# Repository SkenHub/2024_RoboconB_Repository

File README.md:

# 2024_RoboconB_Repository
2024年ロボコンBチーム共有用リポジトリ

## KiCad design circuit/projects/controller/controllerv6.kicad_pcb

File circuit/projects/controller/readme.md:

# 回路系のピン
## コントローラ  
buttonPin1 = 35; 
buttonPin2 = 26;
buttonPin3 = 33;
buttonPin4 = 25;
buttonPin5 = 17;
buttonPin6 = 18;
buttonPin7 = 5;
buttonPin8 = 19;
buttonPin9 = 34;
buttonPin10 = 32; 
buttonPin11 = 21;
IM920,RX:ESP32TX,23
IM920,TX:ESP32RX,22
LED1:GPIO13
LED2:GPIO14
LED3:GPIO27
const int sw[11] = {35,26,33,25,17,18,5,19,34,32,21}; 
# 過去のコントローラ基板のデータはcontroller-backupsの中にzipファイル形式であります．

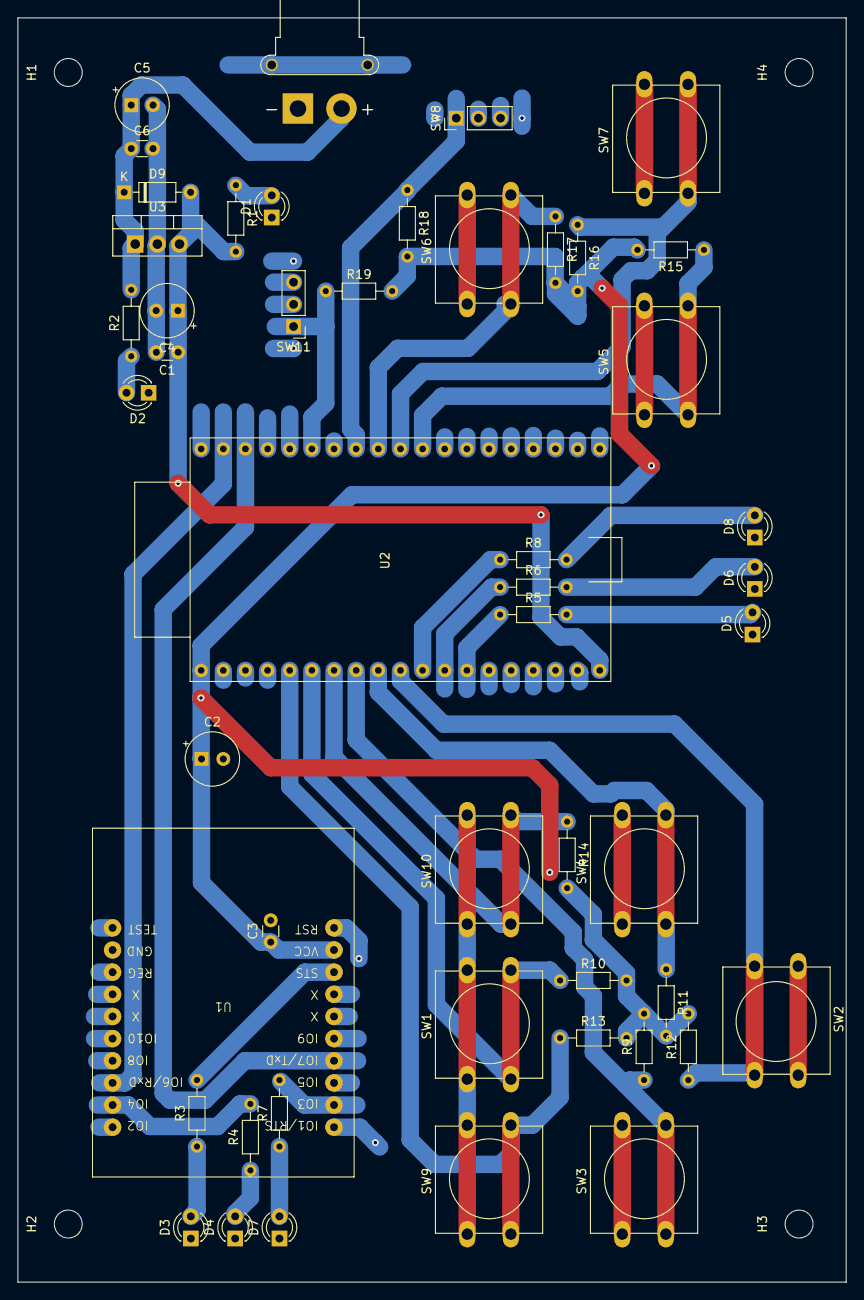
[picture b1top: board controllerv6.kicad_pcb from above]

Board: 2 copper layers, 95.0 x 145.0 mm, 53 parts (0 on the bottom side), 31 nets.

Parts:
C1, C3, C6: 0.1μ; C_Disc_D3.0mm_W1.6mm_P2.50mm
C2, C4, C5: 10μ; CP_Radial_Tantal_D6.0mm_P2.50mm
D1, D2, D3, D4, D5, D6, D7, D8: LED; LED_D3.0mm
D9: D; D_DO-35_SOD27_P7.62mm_Horizontal
H1, H2, H3, H4: MountingHole; MountingHole_3.2mm_M3
J1: Conn_01x02; AMASS_XT30PW-F_1x02_P2.50mm_Horizontal
R1, R2, R3, R4, R7: R; R_Axial_DIN0204_L3.6mm_D1.6mm_P7.62mm_Horizontal
R5, R6, R8: 1k; R_Axial_DIN0204_L3.6mm_D1.6mm_P7.62mm_Horizontal
R9, R10, R11, R12, R13, R14, R15, R16, R17, R18, R19: 10k; R_Axial_DIN0204_L3.6mm_D1.6mm_P7.62mm_Horizontal
SW1, SW2, SW3, SW4, SW5, SW6, SW7, SW9, SW10: SW_DIP_x01; SW_PUSH-12mm
SW8, SW11: TOGGLE; PinHeader_1x03_P2.54mm_Vertical
U1: IM920sL; IM920c-ADP_1
U2: ESP32
U3: LM7805_TO220; TO-220-3_Vertical

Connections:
+3.3V: C2.1, C3.1, R9.2, R10.2, R11.2, R12.2, R13.2, R14.2, R15.2, R16.2, R17.2, R18.2, R19.2, U1.17 (VCC), U2.1 (3V3)
+5V: C1.1, C4.1, D9.2 (A), R1.2, U2.19 (5V), U3.3 (VO)
+BATT: C5.1, C6.1, D9.1 (K), J1.2, R2.2, U3.1 (VI)
GND: C1.2, C2.2, C3.2, C4.2, C5.2, C6.2, D1.1 (K), D2.1 (K), D3.1 (K), D4.1 (K), D5.1 (K), D6.1 (K), D7.1 (K), D8.1 (K), J1.1, SW1.1, SW2.1, SW3.1, SW4.1, SW5.1, SW6.1, SW7.1, SW8.2, SW9.1, SW10.1, SW11.2, U1.18 (GND), U2.14 (GND), U3.2 (GND)
IM920RX: U1.6 (IO6/RxD), U2.37 (23/GPIO23)
IM920TX: U1.7 (IO7/TxD), U2.36 (22/GPIO22)
LED1: R5.1, U2.13 (MTDI/GPIO13/13)
LED2: R6.1, U2.12 (MTMS/GPIO14/14)
LED3: R8.1, U2.11 (GPIO27/27)
unnamed: D1.2 (A), R1.1
unnamed: D2.2 (A), R2.1
unnamed: D3.2 (A), R3.1
unnamed: D4.2 (A), R4.1
unnamed: D5.2 (A), R5.2
unnamed: D6.2 (A), R6.2
unnamed: D7.2 (A), R7.1
unnamed: D8.2 (A), R8.2
SLEEP: R4.2, U1.4 (IO4)
STATUS: R3.2, U1.15 (STATUS)
XMIT: R7.2, U1.3 (IO3)
sw1: R10.1, SW1.2, U2.6 (GPIO35/35)
sw2: R12.1, SW2.2, U2.10 (GPIO26/26)
sw3: R9.1, SW3.2, U2.8 (GPIO33/33)
sw4: R11.1, SW4.2, U2.9 (GPIO25/25)
sw5: R15.1, SW5.2, U2.28 (17/GPIO17)
sw6: R17.1, SW6.2, U2.30 (18/GPIO18)
sw7: R16.1, SW7.2, U2.29 (5/GPIO5)
sw8: R18.1, SW8.1 (O), U2.31 (19/GPIO19)
sw9: R13.1, SW9.2, U2.5 (GPIO34/34)
sw10: R14.1, SW10.2, U2.7 (GPIO32/32)
sw11: R19.1, SW11.1 (O), U2.33 (21/GPIO21)

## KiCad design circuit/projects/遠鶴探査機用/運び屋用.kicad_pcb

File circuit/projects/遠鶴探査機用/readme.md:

# 回路系のピン
## 遠鶴探査機  
SERVO1:D5  
SERVO2:D6  
M1IN1:A1  
M1IN2:A0  
M2IN1:A4  
M2IN2:A5  
IM920RX:D10
IM920TX:D9

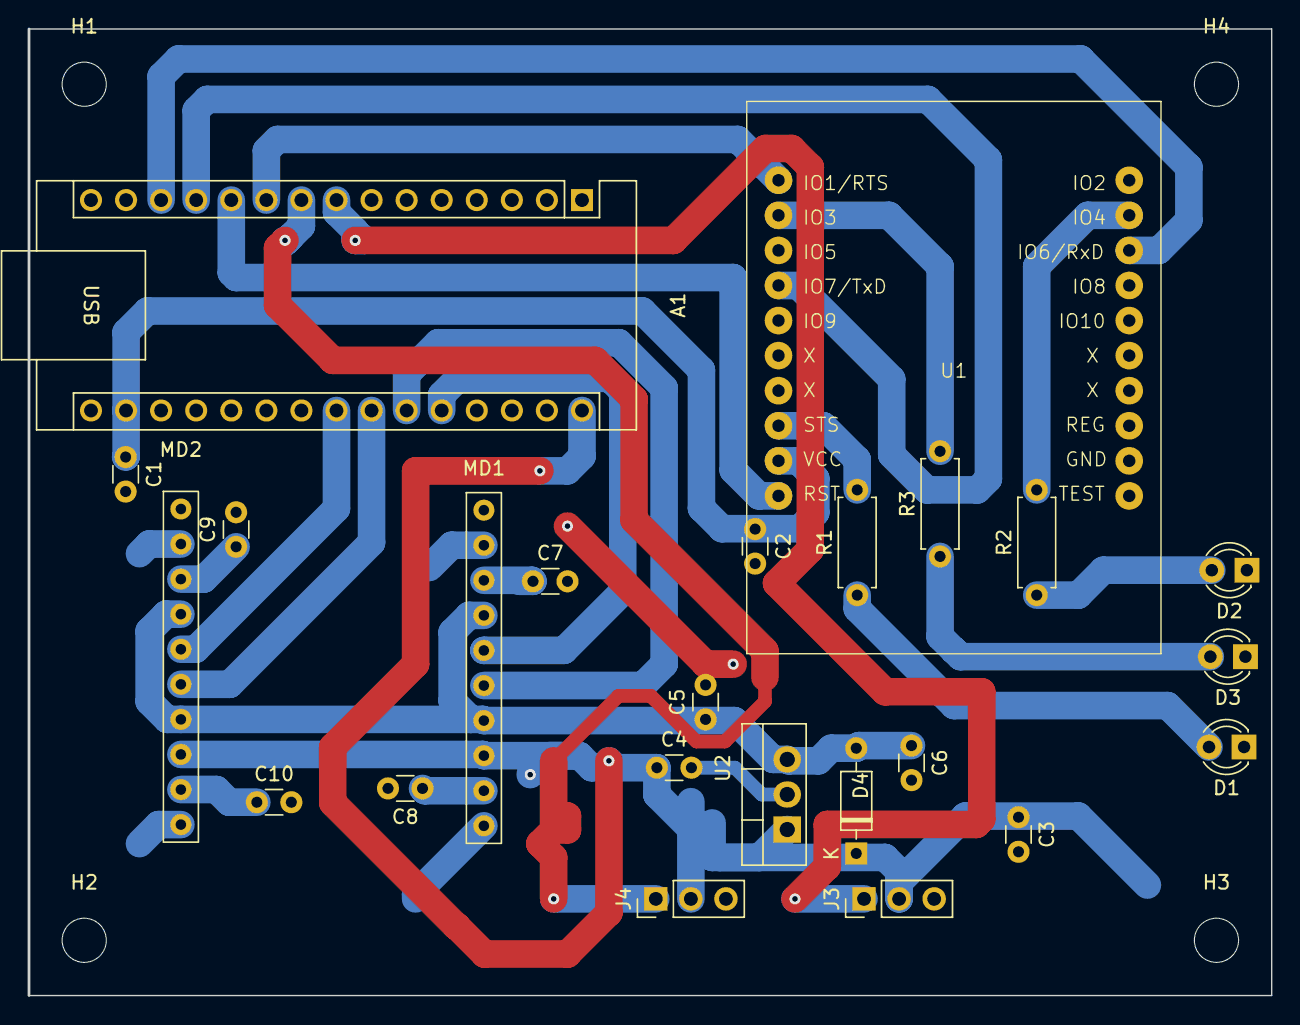
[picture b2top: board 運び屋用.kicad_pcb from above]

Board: 2 copper layers, 90.0 x 70.0 mm, 28 parts (0 on the bottom side), 24 nets.

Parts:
A1: Arduino_Nano_Every; Arduino_Nano
C1, C2, C4, C5: 10μ; C_Disc_D3.0mm_W1.6mm_P2.50mm
C3, C6: 0.1μ; C_Disc_D3.0mm_W1.6mm_P2.50mm
C7, C8, C9, C10: C; C_Disc_D3.0mm_W1.6mm_P2.50mm
D1, D2, D3: LED; LED_D3.0mm
D4: D; D_DO-35_SOD27_P7.62mm_Horizontal
H1, H2, H3, H4: MountingHole; MountingHole_3.2mm_M3
J3, J4: Conn_01x03; PinHeader_1x03_P2.54mm_Vertical
MD1, MD2: BA6222
R1, R2, R3: R; R_Axial_DIN0207_L6.3mm_D2.5mm_P7.62mm_Horizontal
U1: IM920sL; IM920c-ADP_1
U2: LM7805_TO220; TO-220-3_Vertical

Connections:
+3.3V: A1.17 (3V3), C1.1, C2.1, U1.17 (VCC)
+5V: C5.1, C6.1, D4.2 (A), MD1.4 (VR), MD1.7 (VCC1), MD2.4 (VR), MD2.7 (VCC1), U2.3 (VO)
+BATT: A1.30 (VIN), C3.1, C4.1, D4.1 (K), J3.2, J4.2, MD1.8 (VCC2), MD2.8 (VCC2), U2.1 (VI)
BUSY: A1.10 (D7), U1.1 (IO1/RTS/BUSY)
GND: A1.4 (GND), A1.29 (GND), C1.2, C2.2, C3.2, C4.2, C5.2, C6.2, C7.2, C8.2, C9.2, C10.2, D1.1 (K), D2.1 (K), D3.1 (K), J3.3, J4.3, MD1.1 (GND), MD2.1 (GND), U1.18 (GND), U2.2 (GND)
M1IN1: A1.26 (A7), MD1.5 (IN1)
M1IN2: A1.25 (A6), MD1.6 (IN2)
M2IN1: A1.23 (SDA/A4), MD2.5 (IN1)
M2IN2: A1.24 (SCL/A5), MD2.6 (IN2)
unnamed: D1.2 (A), R1.1
unnamed: D2.2 (A), R2.1
unnamed: D3.2 (A), R3.1
unnamed: C7.1, MD1.3 (CD1)
unnamed: C8.1, MD1.9 (CD2)
unnamed: C9.1, MD2.3 (CD1)
unnamed: C10.1, MD2.9 (CD2)
RESET: A1.11 (D8), U1.19 (RESET)
RX920: A1.13 (D10), U1.6 (IO6/RxD)
SERVO1: A1.8 (D5), J3.1
SERVO2: A1.9 (D6), J4.1
SLEEP: R2.2, U1.4 (IO4)
STATUS: R1.2, U1.15 (STATUS)
TX920: A1.12 (D9), U1.7 (IO7/TxD)
XMIT: R3.2, U1.3 (IO3)

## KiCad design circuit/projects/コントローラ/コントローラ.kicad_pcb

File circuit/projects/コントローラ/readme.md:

# 回路系のピン
## コントローラ  
sw1:GPIO34  
sw2:GPIO35  
sw3:GPIO32  
sw4:GPIO33  
sw5:GPIO19  
sw6:GPIO18  
sw7:GPIO05  
sw8:GPIO17  
IM920RX:TX  
IM920TX:RX  
LED1:GPIO25  
LED2:GPIO26
LED3:GPIO27

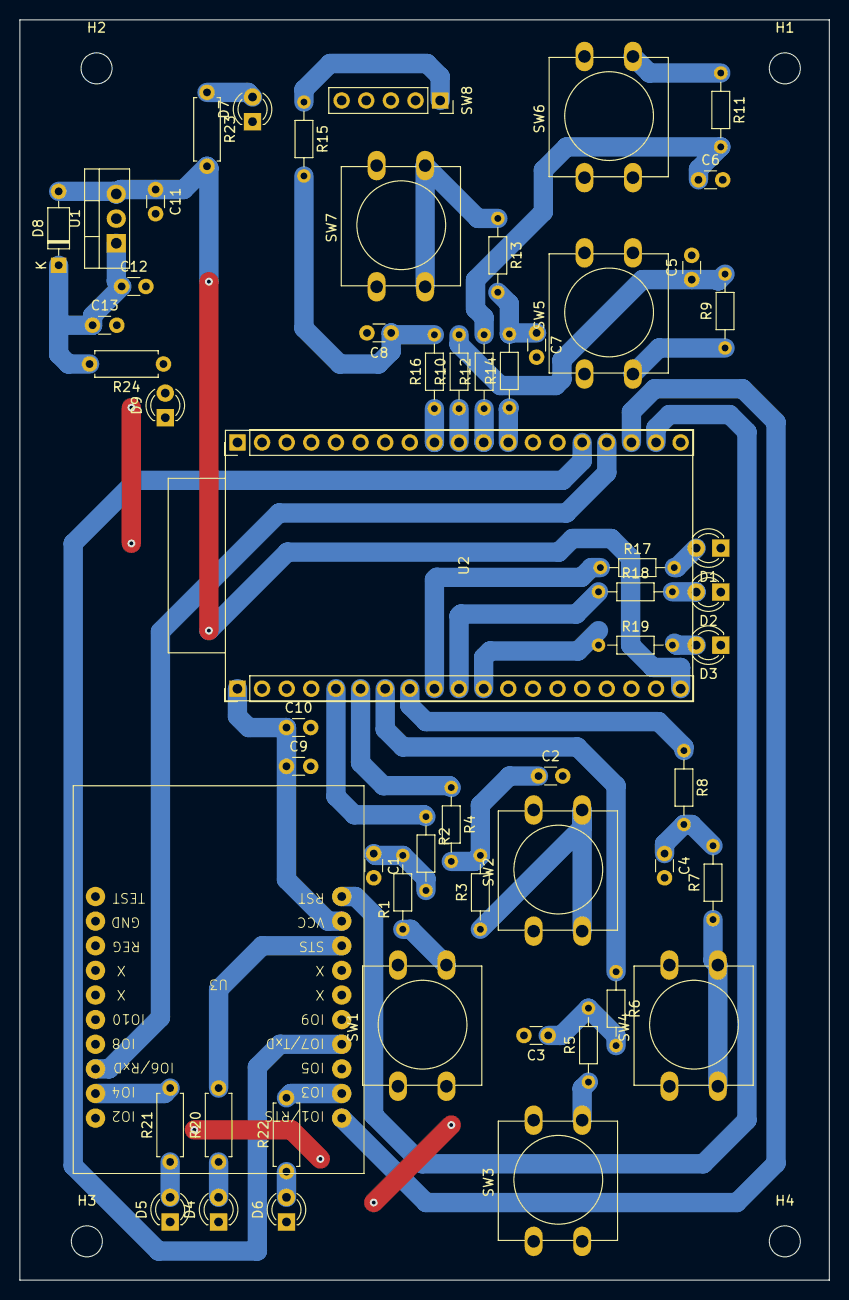
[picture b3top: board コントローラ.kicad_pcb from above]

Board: 2 copper layers, 83.5 x 130.0 mm, 61 parts (0 on the bottom side), 46 nets.

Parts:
C1, C2, C3, C4, C5, C6, C7, C8: C; C_Disc_D3.0mm_W1.6mm_P2.50mm
C9, C12: 0.1μ; C_Disc_D3.0mm_W1.6mm_P2.50mm
C10, C11, C13: 10μ; C_Disc_D3.0mm_W1.6mm_P2.50mm
D1, D2, D3, D4, D5, D6, D7, D9: LED; LED_D3.0mm
D8: D; D_DO-35_SOD27_P7.62mm_Horizontal
H1, H2, H3, H4: MountingHole; MountingHole_3.2mm_M3
R1, R3, R5, R7, R9, R11, R13, R15: 100; R_Axial_DIN0204_L3.6mm_D1.6mm_P7.62mm_Horizontal
R2, R4, R6, R8, R10, R12, R14, R16, R17, R18, R19: 1k; R_Axial_DIN0204_L3.6mm_D1.6mm_P7.62mm_Horizontal
R20, R21, R22, R23, R24: R; R_Axial_DIN0207_L6.3mm_D2.5mm_P7.62mm_Horizontal
SW1, SW2, SW3, SW4, SW5, SW6, SW7: SW_DIP_x01; SW_PUSH-12mm
SW8: TOGGLE; PinSocket_1x05_P2.54mm_Vertical
U1: LM7805_TO220; TO-220-3_Vertical
U2: ESP32; ESP32-DevKitC
U3: IM920sL; IM920c-ADP_1

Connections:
+3.3V: C9.1, C10.1, U2.1 (3V3), U3.17 (VCC)
+5V: C11.1, D8.2 (A), R23.2, U1.3 (VO), U2.19 (5V)
+BATT: C12.1, C13.1, D8.1 (K), R24.2, U1.1 (VI)
BUSY: U2.36 (22/GPIO22), U3.1 (IO1/RTS/BUSY)
GND: C1.2, C2.2, C3.2, C4.2, C5.2, C6.2, C7.2, C8.2, C9.2, C10.2, C11.2, C12.2, C13.2, D1.1 (K), D2.1 (K), D3.1 (K), D4.1 (K), D5.1 (K), D6.1 (K), D7.1 (K), D9.1 (K), SW1.1, SW2.1, SW3.1, SW4.1, SW5.1, SW6.1, SW7.1, SW8.2, U1.2 (GND), U2.14 (GND), U3.18 (GND)
IM920RX: U2.35 (TX/UOTXD), U3.6 (IO6/RxD)
IM920TX: U2.34 (RX/UORXD), U3.7 (IO7/TxD)
unnamed: C1.1, R1.2, R2.2
unnamed: C2.1, R3.2, R4.2
unnamed: C3.1, R5.2, R6.2
unnamed: C4.1, R7.2, R8.2
unnamed: C5.1, R9.2, R10.2
unnamed: C6.1, R11.2, R12.2
unnamed: C7.1, R13.2, R14.2
unnamed: C8.1, R15.2, R16.2
unnamed: D1.2 (A), R17.2
unnamed: D2.2 (A), R18.2
unnamed: D3.2 (A), R19.2
unnamed: D4.2 (A), R20.1
unnamed: D5.2 (A), R21.1
unnamed: D6.2 (A), R22.1
unnamed: D7.2 (A), R23.1
unnamed: D9.2 (A), R24.1
unnamed: R1.1, SW1.2
unnamed: R3.1, SW2.2
unnamed: R5.1, SW3.2
unnamed: R7.1, SW4.2
unnamed: R9.1, SW5.2
unnamed: R11.1, SW6.2
unnamed: R13.1, SW7.2
unnamed: R15.1, SW8.1 (O)
unnamed: R17.1, U2.9 (GPIO25/25)
unnamed: R18.1, U2.10 (GPIO26/26)
unnamed: R19.1, U2.11 (GPIO27/27)
RESET: U2.37 (23/GPIO23), U3.19 (RESET)
SLEEP: R21.2, U3.4 (IO4)
STATUS: R20.2, U3.15 (STATUS)
XMIT: R22.2, U3.3 (IO3)
sw1: R2.1, U2.5 (GPIO34/34)
sw2: R4.1, U2.6 (GPIO35/35)
sw3: R6.1, U2.7 (GPIO32/32)
sw4: R8.1, U2.8 (GPIO33/33)
sw5: R16.1, U2.28 (17/GPIO17)
sw6: R10.1, U2.29 (5/GPIO5)
sw7: R12.1, U2.30 (18/GPIO18)
sw8: R14.1, U2.31 (19/GPIO19)

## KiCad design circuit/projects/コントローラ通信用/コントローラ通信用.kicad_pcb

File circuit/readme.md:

# 回路系共有用フォルダー
# 回路系のピン
## コントローラ
buttonPin1 = 35; 
buttonPin2 = 26;
buttonPin3 = 33;
buttonPin4 = 25;
buttonPin5 = 17;
buttonPin6 = 18;
buttonPin7 = 5;
buttonPin8 = 19;
buttonPin9 = 34;
buttonPin10 = 32; 
buttonPin11 = 21;
IM920,RX:ESP32TX,23
IM920,TX:ESP32RX,22
LED1:GPIO13
LED2:GPIO14
LED3:GPIO27
const int sw[11] = {35,26,33,25,17,18,5,19,34,32,21}; 
## 遠鶴探査機  
SERVO1:D5  
SERVO2:D6  
M1IN1:A0  
M1IN2:A1  
M2IN1:A4  
M2IN2:A5  
IM920RX:D10
IM920TX:D9

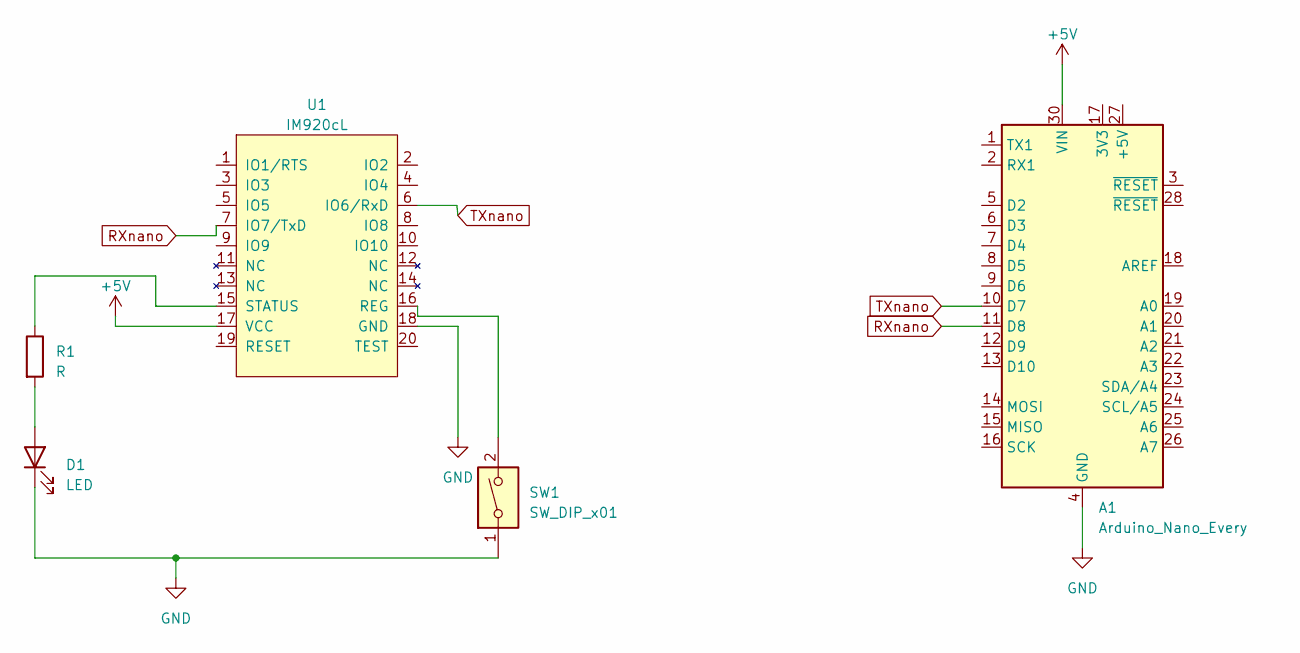
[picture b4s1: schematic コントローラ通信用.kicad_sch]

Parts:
A1: Arduino_Nano_Every; Arduino_Nano
D1: LED; LED_D3.0mm
R1: R; R_Axial_DIN0204_L3.6mm_D1.6mm_P1.90mm_Vertical
SW1: SW_DIP_x01; SW_PUSH-12mm
U1: IM920cL; IM920c-ADP_1

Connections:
+5V: A1.30 (VIN), U1.17 (VCC)
GND: A1.4 (GND), A1.29 (GND), D1.1 (K), SW1.1, U1.18 (GND)
unnamed: D1.2 (A), R1.2
unnamed: SW1.2, U1.16 (REG)
unnamed: R1.1, U1.15 (STATUS)
RXnano: A1.11 (D8), U1.7 (IO7/TxD)
TXnano: A1.10 (D7), U1.6 (IO6/RxD)

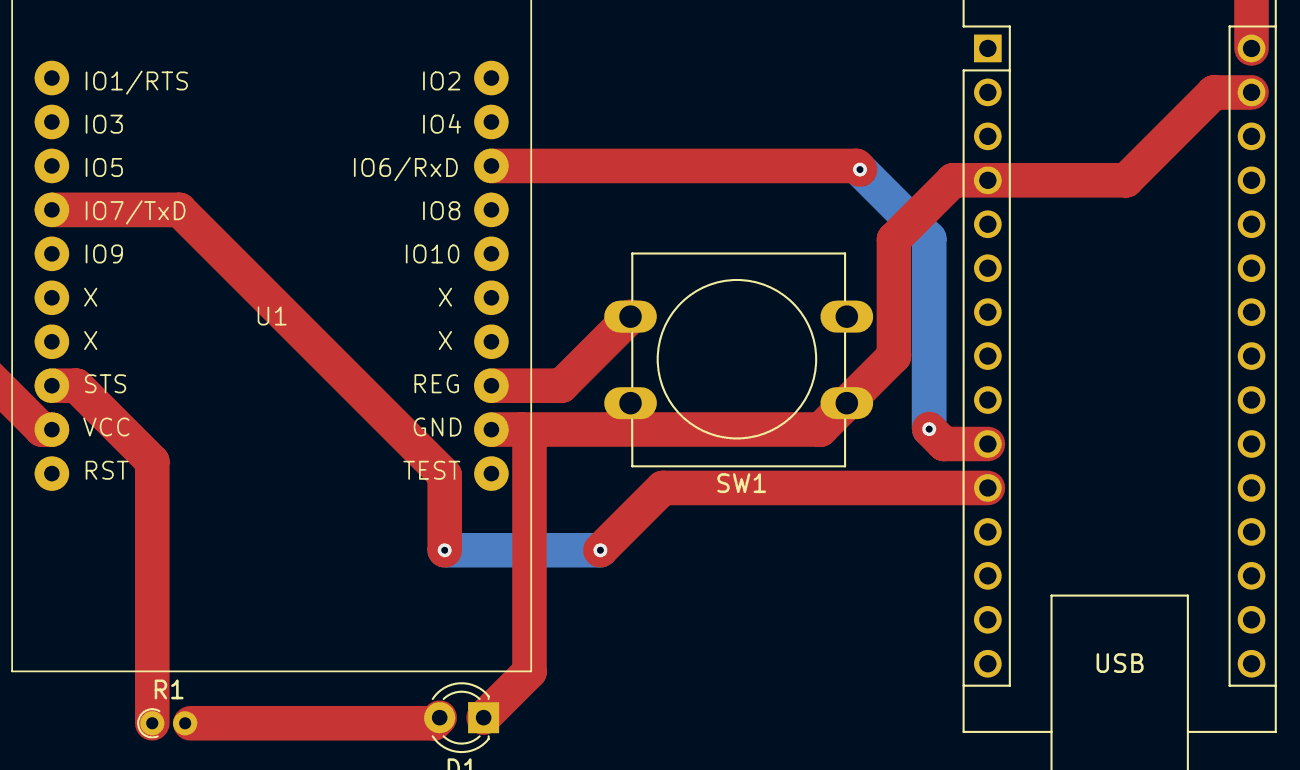
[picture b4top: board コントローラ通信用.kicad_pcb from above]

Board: 2 copper layers, 5 parts (0 on the bottom side), 7 nets.

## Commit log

2024-04-21 各班用フォルダー追加
2024-04-21 readme追加
2024-04-22 robot2_prot_ver1
2024-04-24 サーボの機能を追加
2024-04-24 放物線のシミュレーション
    初速度と射出速度で放物線を生成
    その際の運動エネルギーも表示
2024-04-29 資料追加
2024-04-29 Create IM920c-ADP.pretty.zip
    IM920のシンボルとフットプリントを紐づけたものです
2024-05-01 IM920通信チェック用PCプログラム
    IM920sLをパソコンにつないだ状態で送信のみが可能なプログラム
2024-05-03 受信機能追加
2024-05-04 Arduino用IM920プログラム
2024-05-11 kari
2024-05-12 一応サーボを動かせるように
    ピン番号を指定したらサーボが回ります
    角度は何度にすればいいのか分からないのでとりあえず手動で調整できるようにしておきました
2024-05-14 やっとサーボ回せるように出来た
    LトリガーとRトリガーで動きますわよ
2024-05-14 修正/CO除去
2024-05-16 スティックを倒したらサーボが勝手に動く問題(Issue#23)を解決+α
    原因:PWMのタイマーが被っていたのを修正
    α:メモリ関連が原因だと思っていたので型などを見直しした。など
2024-05-16 余計なコメントを除去
2024-05-18 モーター動い(て)た
    よくわからない
2024-05-20 FAQと修正版ルールブック追加
2024-05-26 金子さんロボット
2024-06-11 ロボット1のROSワークスペース追加
2024-06-13 R1プログラム更新
2024-06-13 R1_ws削除
2024-06-17 鶴パルト回転数チェック用プログラム
    発射物の落下より早く回転するには2rpsが必要
2024-06-17 アイデアシート6/17追加
2024-06-17 ロボ2（投石器）の実験のプログラム
2024-06-17 第二回FAQ追加
2024-06-18 IM920Arduino用ライブラリ製作
2024-06-19 torima
2024-06-20 とりあえず動くと信じます
    (比較演算子のORとビット演算子のORを間違えてたなんて言えない)
2024-06-21 kanekosan2 zyusin
2024-06-22 送信側プログラム
2024-06-23 存在しないピンに定義していたのを修正
2024-06-23 大量にあった謎のコメントアウトを除去
    なぜ絶対使わないであろうコードがコメントアウトされた状態で残ってたんだ?
2024-06-23 鶴明STMプログラム追加
2024-06-28 現時点でのプログラム
2024-07-01 最新かねこさん受信
2024-07-01 最新かねこさん送信
2024-07-01 proguram_update
2024-07-02 回路の追加
2024-07-02 IM920ピン番号修正
2024-07-03 名前変更
2024-07-03 遠鶴探索機プログラム名変更
2024-07-04 速度調整、回転方向の逆転ボタンを追加
2024-07-09 なんかb入ってました
2024-07-09 ルールブック、FAQ更新
2024-07-12 esp仕様に変更
2024-07-12 updateしました
2024-07-13 鶴明、鶴パルトコントローラー追加
2024-07-13 readmeのpin番号の修正とコントローラのswの番号の変更による基板の設計の調整
2024-07-13 ESPのフットプリント違ったので修正します
2024-07-13 加工データ追加
2024-07-15 readmeを更新
2024-07-20 ピン番号の更新と回路データの更新
2024-08-19 8/20
2024-08-21 提出資料
2024-08-22 最終アイデアシート完成
2024-08-23 8/23
2024-08-31 鶴明、鶴パルト
2024-09-13 鶴明射出ラッチ2個に変更
2024-09-13 鶴パルトPS4コントローラ復活
2024-09-24 コメントアウトの削除など
2024-09-28 ボールをつかむ角度を追加
2024-10-02 使用サーボ変更ver
